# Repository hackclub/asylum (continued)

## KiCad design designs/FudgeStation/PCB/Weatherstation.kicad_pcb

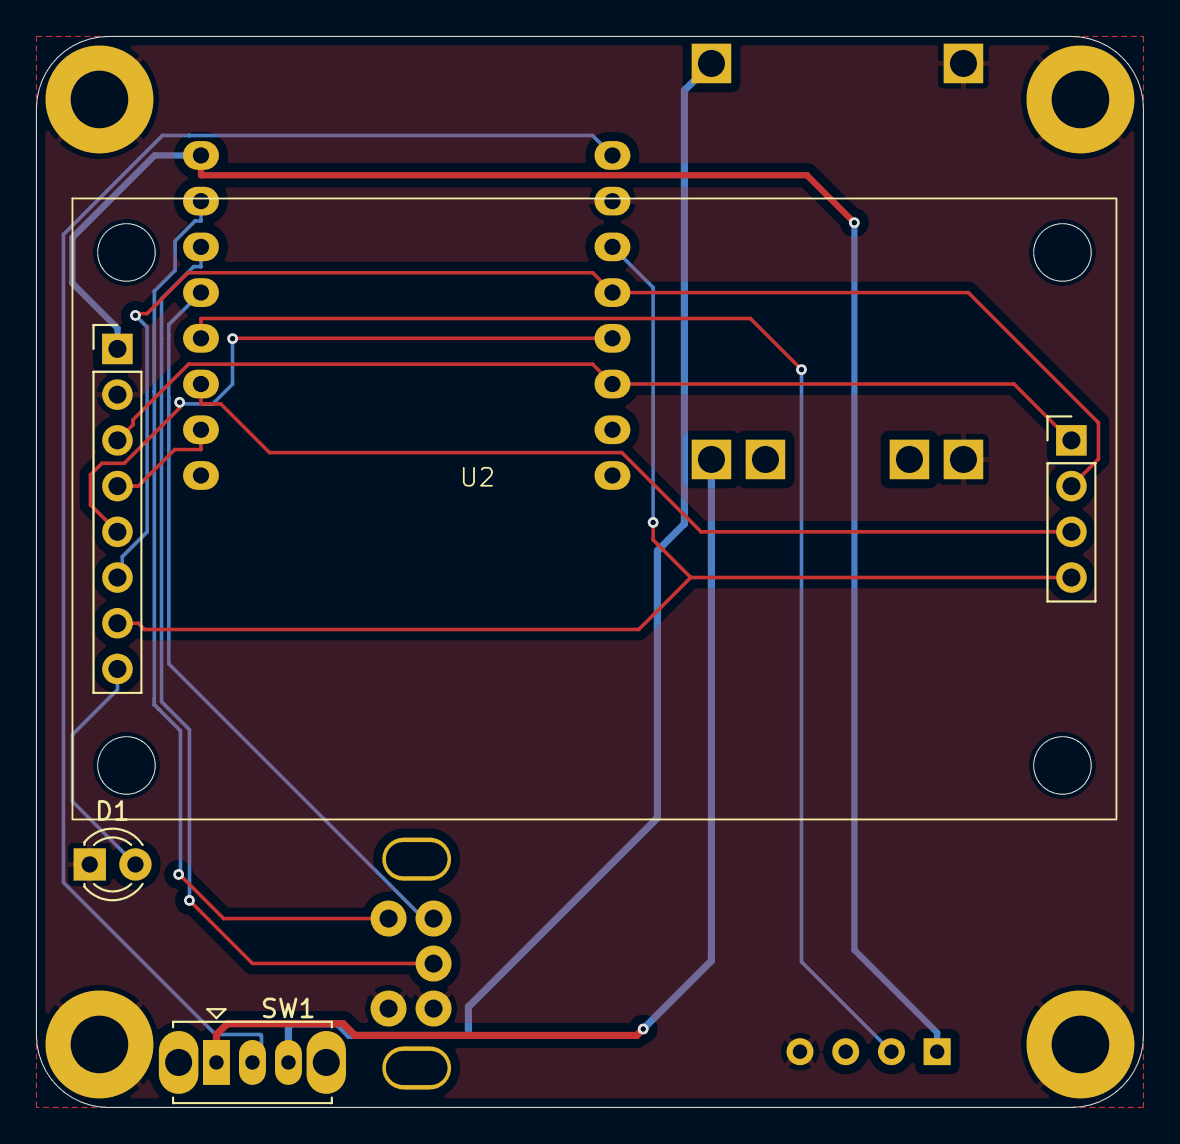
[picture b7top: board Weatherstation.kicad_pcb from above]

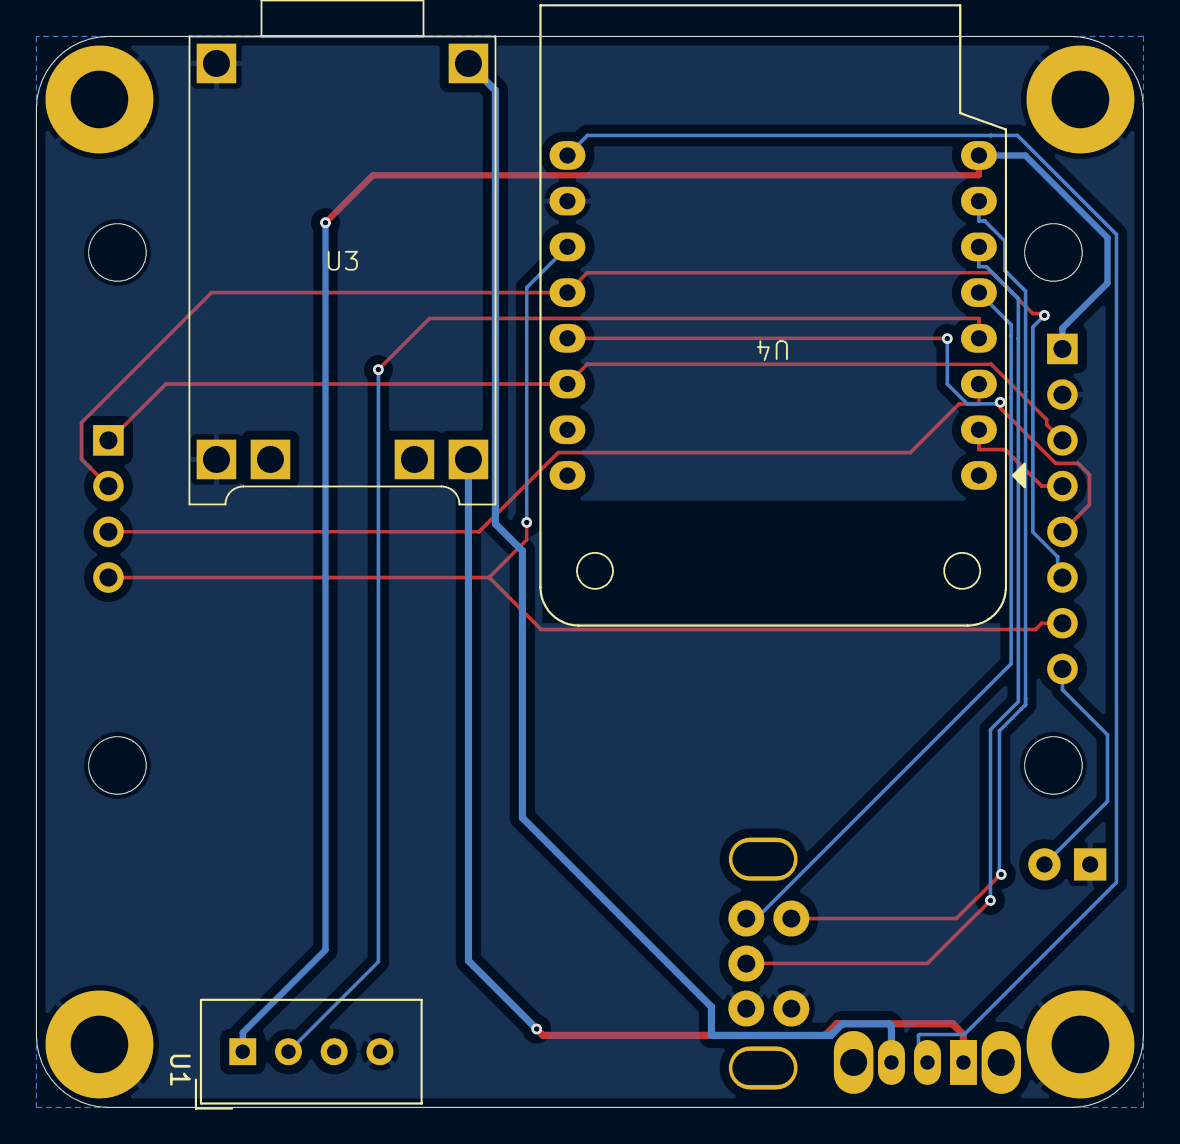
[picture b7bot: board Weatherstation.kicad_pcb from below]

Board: 2 copper layers, 61.5 x 59.5 mm, 11 parts (3 on the bottom side), 16 nets.

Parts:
D1: LED_3mm; LED_D3.0mm
H1, H2, H3, H4: MountingHole_M3_3.2mm_Pad; MountingHole_3.2mm_Pad
SW1: SW_SPDT; SW_Slide_SPDT_Straight_CK_OS102011MS2Q
U1: DHT11; Aosong_DHT11_5.5x12.0_P2.54mm
U2: TFT_ST7735_SD
U3: TP4056
U4: WEMOS_C3_Mini; WEMOS_C3_mini
U5: EC11B; RotaryEncoder_EC11B-Horizontal-Dual

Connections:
+3V3: U1.1 (VDD), U2.1 (3V3), U4.8 (3V3)
CS: U2.3 (LCD_CS), U2.9 (SD_CS), U4.14 (CS0/IO10)
DATA: U1.2 (DATA), U4.4 (IO1)
D/C: U2.5 (D/C), U4.13 (IO8)
EN: U2.4 (EN), U4.2 (IO3)
ENC_A: U4.5 (IO0), U5.B
ENC_B: U4.6 (IO4), U5.C
ENC_C: U4.7 (IO5), U5.S2
GND: D1.1, H1.1, H2.1, H3.1, H4.1, U1.4 (GND), U2.2 (GND), U3.3 (OUT-), U3.5 (IN-), U4.10 (GND), U5.A, U5.S1
MISO: U2.11 (SD_MISO), U4.3 (MISO/IO2)
MOSI: U2.6 (LCD_MOSI), U2.10 (SD_MOSI), U4.12 (MOSI/IO7)
unnamed: SW1.2 (B), U4.9 (5V)
unnamed: D1.2, U2.8 (LED)
SCK: U2.7 (LCD_SCK), U2.12 (SD_SCK), U4.11 (SCK/IO6)
TP_input: SW1.3 (C), U3.4 (IN+)
VCC: SW1.1 (A), U3.2 (OUT+)

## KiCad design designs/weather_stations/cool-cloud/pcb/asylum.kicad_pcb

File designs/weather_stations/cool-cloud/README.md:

# Here is my submission for the weather station 
It uses the display to show current weather and a forecast 
Instead of a case, I will put this in an old box that I have and fill it with cotton to make it look like a cloud. 

# PCB

[] I ran DRC in KiCad and have made sure there are 0 errors!

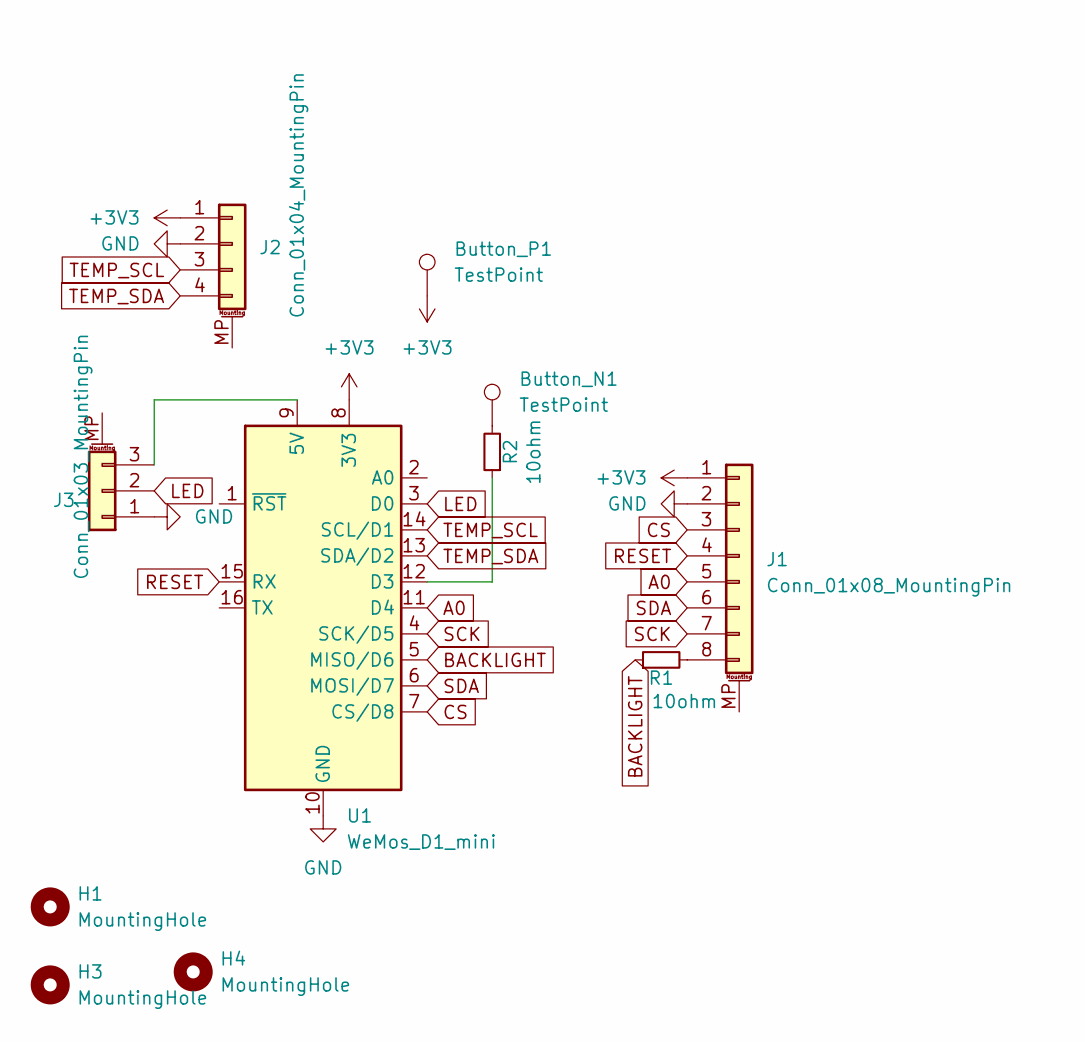
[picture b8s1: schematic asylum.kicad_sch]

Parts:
Button_N1: TestPoint; TestPoint_Pad_2.5x2.5mm
Button_P1: TestPoint; TestPoint_Pad_2.5x2.5mm
H1, H3, H4: MountingHole; MountingHole_2.7mm_M2.5
J1: Conn_01x08_MountingPin; PinHeader_1x08_P2.54mm_Vertical
J2: Conn_01x04_MountingPin; PinHeader_1x04_P2.54mm_Vertical
J3: Conn_01x03_MountingPin; PinHeader_1x03_P2.54mm_Vertical
R1, R2: 10ohm; C_0201_0603Metric_Pad0.64x0.40mm_HandSolder
U1: WeMos_D1_mini; WEMOS_D1_mini_light

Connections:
+3V3: Button_P1.1, J1.1, J2.1, U1.8 (3V3)
A0: J1.5, U1.11 (D4)
BACKLIGHT: R1.1, U1.5 (MISO/D6)
CS: J1.3, U1.7 (CS/D8)
GND: J1.2, J2.2, J3.1, U1.10 (GND)
LED: J3.2, U1.3 (D0)
unnamed: Button_N1.1, R2.2
unnamed: J1.8, R1.2
unnamed: J3.3, U1.9 (5V)
unnamed: R2.1, U1.12 (D3)
RESET: J1.4, U1.15 (RX)
SCK: J1.7, U1.4 (SCK/D5)
SDA: J1.6, U1.6 (MOSI/D7)
TEMP_SCL: J2.3, U1.14 (SCL/D1)
TEMP_SDA: J2.4, U1.13 (SDA/D2)

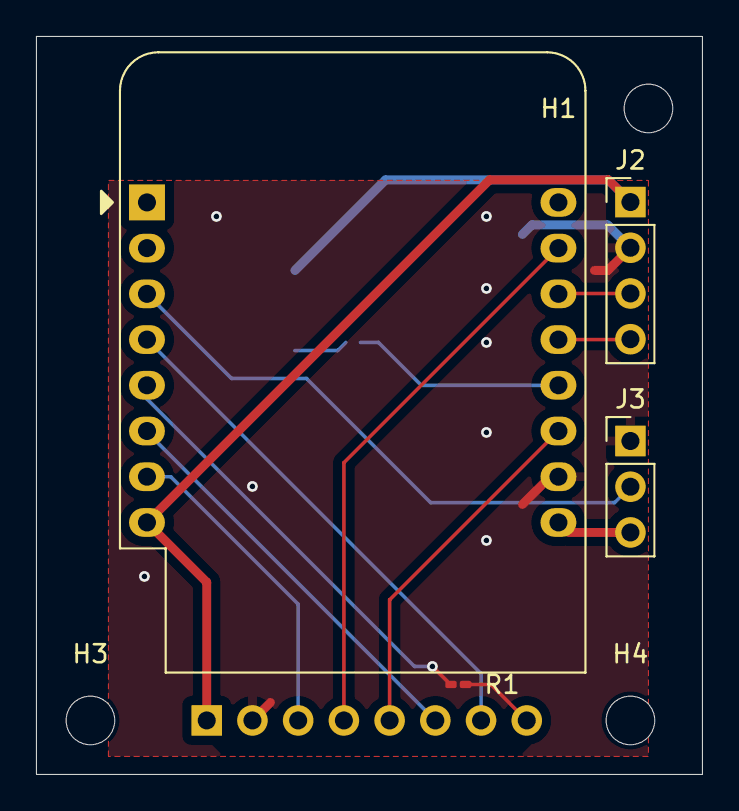
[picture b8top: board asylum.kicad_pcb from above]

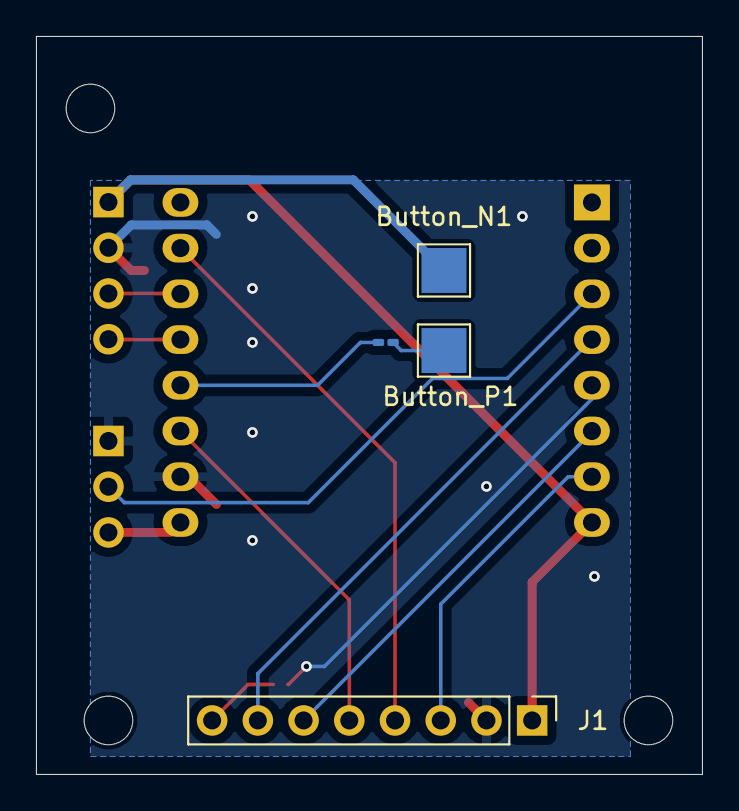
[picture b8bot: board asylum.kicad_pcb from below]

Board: 2 copper layers, 37.0 x 41.0 mm, 11 parts (4 on the bottom side), 15 nets.

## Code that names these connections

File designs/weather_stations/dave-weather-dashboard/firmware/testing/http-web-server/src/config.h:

#ifndef CONFIG_H
#define CONFIG_H

#define hotspot_ssid "change-with-your-hotspot-ssid"
#define hotspot_password "change-with-your-hotspot-password"
#define wifi_ssid  "change-with-your-wifi-ssid"
#define wifi_password "change-with-your-wifi-password"
#define reconnect_attempts 3
#define reconnect_interval 5000
#define hostname "weather-station"
#define BMKG_API_BASE "https://api.bmkg.go.id"
#define BMKG_KODE_WILAYAH_TINGKAT_IV "change-with-kode-wilayah"
#define REFRESH_INTERVAL 30 * 60 * 1000
#define BOUNCE_INTERVAL 50

// Pins configuration
#define TFT_CS 20
#define TFT_DC 21
#define TFT_EN 28
#define MOSI 27
#define MISO 15
#define SCK 19
#define SD_CS 14
#define REFRESH_BUTTON 5

#endif

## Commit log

2024-12-23 upload m0hid-dash
2024-12-24 Added case/stand file
2024-12-24 Dave's Weather Dashboard :)
2024-12-24 NFC keychain submission
2024-12-25 3D model revisions
2025-01-03 Magic nfc kaytags submission
2025-01-05 Souptik
2025-01-05 Removed archive, and gerber to order
2025-01-12 Christmas Crest
    This is a Christmas Tree Leaf shaped keychain
2025-01-12 Create CircuitCyborg NFC Tag
2025-01-12 CircuitCyborg NFC Tag
2025-01-12 add keychain
2025-01-13 Added aeroportal
2025-01-13 Add step file
2025-01-18 Removed external resistor to use internal resistor and added load sharing circuit along with updated casing
2025-01-18 Add my design
    Rick and morty themed design
2025-01-18 Add files via upload
    adjusted the size the other one had the diameter set to 3 inches
2025-01-20 Resubmitting to correct repo
2025-01-23 Add aniweather
2025-01-24 done :)
2025-01-25 waffle made
2025-01-25 Rename geo_design + filet.stl to geo_design + filet.stl
2025-01-26 add pcb, case, and readme
2025-01-26 piplup keytag!!
2025-01-26 add basic firmware
2025-01-26 update bom
2025-01-26 Add cyao keychain
2025-01-27 Removed extra parts
2025-01-27 Rename NFC-Hash-AK.stp to Hash-AK.stp
2025-01-27 Delete designs/nfc_keytag/Hash-AK-NFC/Hash-AK.stp
    Trying to fix stuff
2025-01-27 Rename NFC keychain(1).stl to Hash-AK-keytag.stl
2025-01-27 Submission of Hack Club Asylum NFC keytag
2025-01-27 new file: designs/weather_stations/Crabbys605's station/code/Main.cpp new file: designs/weather_stations/Crabbys605's station/pcb/Untitled v0.f3d new file: designs/weather_stations/Crabbys605's stati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
2025-01-27 Added image
2025-01-27 Create first
2025-01-27 Create new
2025-01-27 Remove keychain
2025-01-27 Create Codelife's NFC submission
2025-01-27 Add cyaotag
2025-01-27 Reformat folder names
2025-01-27 Addinh My Weather Station
2025-01-27 fix submission
2025-01-27 Reexport step
2025-01-27 update to required directory structure
2025-01-28 Rename designs/nfc_keytags/3XAY_keychain.stl to designs/nfc_keytags/3XAYNFC/3XAY_keychain.stl
2025-01-28 Upload submission files
2025-01-28 Added step file & picture
2025-01-28 Added step file and picture
2025-01-28 Add files via upload
    A .step file was too big to be uploaded
2025-01-28 add image to readme
2025-01-28 fix image
2025-01-28 Create c
2025-01-28 Create n\
2025-01-29 Added README and image to keychain
2025-01-31 fixed format
2025-02-01 made changes
2025-02-01 0.7 -> 0.8
2025-02-01 Rename 408720377-91e1e540-2558-437d-bf1b-7178e54e290f.png to image.png
2025-02-01 Add images and notes
2025-02-01 Fix slack ID
2025-02-01 update ATag
2025-02-02 Updated aeroportal submodule
2025-02-03 SOUPTIK_NFC
2025-02-11 deleted: designs/nfc_keytags/hack_club_keytag/HC Keychain.step
2025-02-11 oops new file: designs/nfc_keytags/hack_club_keytag/HC Keychain.step
2025-02-11 Restore HC Keychain.step file
2025-02-13 Update readme_+_BOM.md
    Added links and itemized costs
2025-02-13 Update to readme_+_BOM.md
    Added an image of the schematic plus a description of what the device will do and some plans for future software versions.
2025-02-13 Added cavity
2025-02-13 Update readme_+_BOM.md
    Reupdated BOM
2025-02-14 removing designs/weather_stations/Jai's Weather Display directory
2025-02-14 adding the weather station
2025-02-17 add cyrilli-weather-station
2025-02-18 Revert "Adding My weather station"
2025-02-19 create cardigan nfc tag + add readme!
2025-02-19 upload cardigan nfc tag step file
2025-02-22 Updated img
2025-02-26 add fudgestation
2025-02-26 Priority Power MUX
2025-02-26 add bom :)
2025-02-28 Updated BOM and casing
2025-02-28 screenshots
